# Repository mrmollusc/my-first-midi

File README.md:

# my-first-midi
mmm midi keypad

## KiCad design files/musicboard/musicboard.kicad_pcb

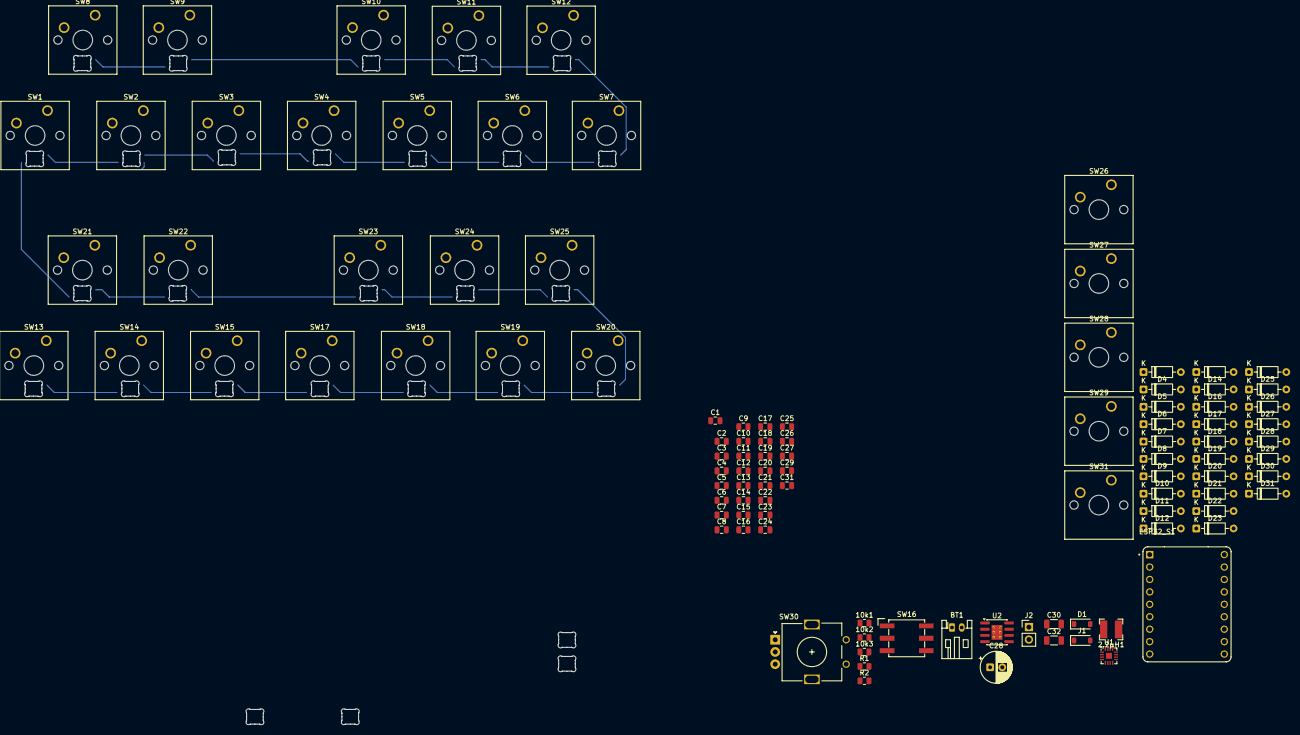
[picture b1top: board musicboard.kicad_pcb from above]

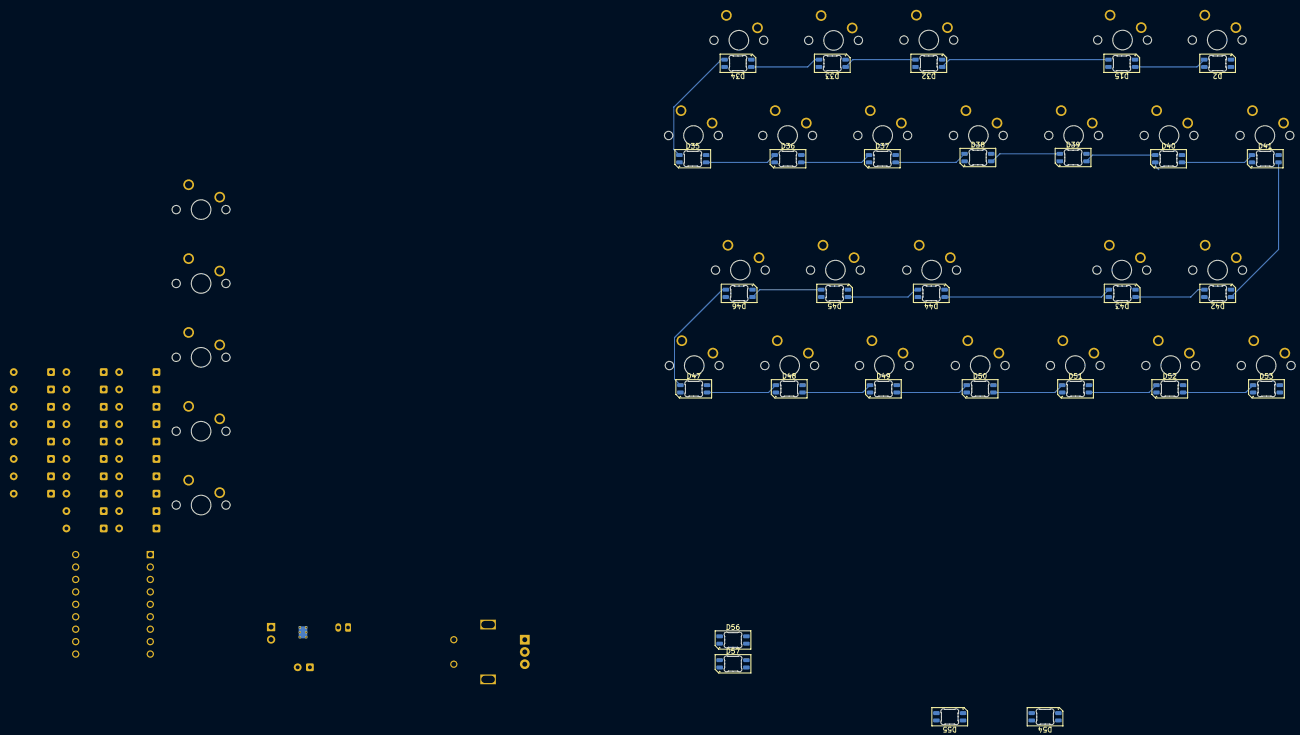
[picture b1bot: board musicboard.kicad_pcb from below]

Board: 2 copper layers, 132 parts (28 on the bottom side), 78 nets.

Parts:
2.2µH1: L_Small; L_Bourns-SRN4018
10k1, 10k2, 10k3: R_Small; R_0805_2012Metric
BT1: Battery_Cell; JST_PH_S2B-PH-K_1x02_P2.00mm_Horizontal
C1, C2, C3, C4, C5, C6, C7, C8, C9, C10, C11, C12, C13, C14, C15, C16, C17, C18, C19, C20, C21, C22, C23, C24, C25, C26, C27, C29, C31: 0.1 µF; C_0805_2012Metric
C28: 470uF; CP_Radial_D6.3mm_P2.50mm
C30: 22 µF; C_1206_3216Metric
C32: 10 µF; C_1206_3216Metric
D1: D_Schottky; D_SOD-123
D2, D15, D32, D33, D34, D35, D36, D37, D38, D39, D40, D41, D42, D43, D44, D45, D46, D47, D48, D49, D50, D51, D52, D53, D54, D55, D56, D57: SK6812MINI-E; LED_SK6812MINI-E_3.2x2.8mm_P1.5mm_ReverseMount
D3, D4, D5, D6, D7, D8, D9, D10, D11, D12, D13, D14, D16, D17, D18, D19, D20, D21, D22, D23, D24, D25, D26, D27, D28, D29, D30, D31: 1N4148; D_DO-35_SOD27_P7.62mm_Horizontal
ESP32_S1: Waveshare ESP32-S3-Zero
J1: Micro_SD_Card; D_SOD-123
J2: Speaker; PinHeader_1x02_P2.54mm_Vertical
R1: 330Ω; R_0805_2012Metric
R2: 1 MΩ; R_0805_2012Metric
SW1, SW2, SW3, SW4, SW5, SW6, SW7, SW8, SW9, SW10, SW11, SW12, SW13, SW14, SW15, SW17, SW18, SW19, SW20, SW21, SW22, SW23, SW24, SW25, SW26, SW27, SW28, SW29, SW31: SW_Push; SW_Cherry_MX_1.00u_PCB
SW16: RotaryEncoder; Nidec_Copal_SH-7010B
SW30: RotaryEncoder; RotaryEncoder_Alps_EC11E_Vertical_H20mm
U1: MAX98357A; TQFN-16-1EP_3x3mm_P0.5mm_EP1.23x1.23mm
U2: IP5306-LC; SOIC-8-1EP_3.9x4.9mm_P1.27mm_EP2.29x3mm_ThermalVias

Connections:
+3.3V: 10k1.2, 10k2.1, 10k3.2
+5V: 2.2µH1.2, C1.1, C2.1, C3.1, C4.1, C5.1, C6.1, C7.1, C8.1, C9.1, C10.1, C11.1, C12.1, C13.1, C14.1, C15.1, C16.1, C17.1, C18.1, C19.1, C20.1, C21.1, C22.1, C23.1, C24.1, C25.1, C26.1, C27.1, C28.1, C29.1, C31.2, C32.2, D1.2 (A), D2.3 (VDD), D15.3 (VDD), D32.3 (VDD), D33.3 (VDD), D34.3 (VDD), D35.3 (VDD), D36.3 (VDD), D37.3 (VDD), D38.3 (VDD), D39.3 (VDD), D40.3 (VDD), D41.3 (VDD), D42.3 (VDD), D43.3 (VDD), D44.3 (VDD), D45.3 (VDD), D46.3 (VDD), D47.3 (VDD), D48.3 (VDD), D49.3 (VDD), D50.3 (VDD), D51.3 (VDD), D52.3 (VDD), D53.3 (VDD), D54.3 (VDD), D55.3 (VDD), D56.3 (VDD), D57.3 (VDD), R2.1, U1.7 (VDD), U1.8 (VDD), U2.8 (VOUT)
/BAT: BT1.1 (+), C30.1, U2.6 (BAT)
/CD: 10k2.2, J1.2 (DAT3/CD_2)
/COL1: SW1.1, SW5.1, SW9.1, SW13.1, SW18.1, SW22.1, SW26.1
/COL2: SW2.1, SW6.1, SW10.1, SW14.1, SW19.1, SW23.1, SW27.1
/COL3: SW3.1, SW7.1, SW11.1, SW15.1, SW20.1, SW24.1, SW28.1
/COL4: SW4.1, SW8.1, SW12.1, SW17.1, SW21.1, SW25.1, SW29.1
/ROW1: D3.1 (K), D4.1 (K), D5.1 (K), D7.1 (K)
/ROW2: D6.1 (K), D8.1 (K), D9.1 (K), D10.1 (K)
/ROW3: D11.1 (K), D12.1 (K), D13.1 (K), D14.1 (K)
/ROW4: D16.1 (K), D17.1 (K), D18.1 (K), D19.1 (K)
/ROW5: D20.1 (K), D21.1 (K), D22.1 (K), D23.1 (K)
/ROW6: D24.1 (K), D25.1 (K), D26.1 (K), D27.1 (K)
/ROW7: D28.1 (K), D29.1 (K), D30.1 (K), D31.1 (K)
/VBUS: D1.1 (K), U2.1 (VIN)
GND: BT1.2 (-), C1.2, C2.2, C3.2, C4.2, C5.2, C6.2, C7.2, C8.2, C9.2, C10.2, C11.2, C12.2, C13.2, C14.2, C15.2, C16.2, C17.2, C18.2, C19.2, C20.2, C21.2, C22.2, C23.2, C24.2, C25.2, C26.2, C27.2, C28.2, C29.2, C30.2, C31.1, C32.1, D2.1 (VSS), D15.1 (VSS), D32.1 (VSS), D33.1 (VSS), D34.1 (VSS), D35.1 (VSS), D36.1 (VSS), D37.1 (VSS), D38.1 (VSS), D39.1 (VSS), D40.1 (VSS), D41.1 (VSS), D42.1 (VSS), D43.1 (VSS), D44.1 (VSS), D45.1 (VSS), D46.1 (VSS), D47.1 (VSS), D48.1 (VSS), D49.1 (VSS), D50.1 (VSS), D51.1 (VSS), D52.1 (VSS), D53.1 (VSS), D54.1 (VSS), D55.1 (VSS), D56.1 (VSS), D57.1 (VSS), SW16.C (C_C), SW30.C, SW31.2, U1.3 (GND), U1.11 (GND), U1.15 (GND), U1.17 (PAD), U2.9 (EP)
unnamed: D2.2 (DIN), R1.2
unnamed: D3.2 (A), SW1.2
unnamed: D4.2 (A), SW2.2
unnamed: D5.2 (A), SW3.2
unnamed: D6.2 (A), SW5.2
unnamed: D7.2 (A), SW4.2
unnamed: D8.2 (A), SW6.2
unnamed: D9.2 (A), SW7.2
unnamed: D10.2 (A), SW8.2
unnamed: D11.2 (A), SW9.2
unnamed: D12.2 (A), SW10.2
unnamed: D13.2 (A), SW11.2
unnamed: D14.2 (A), SW12.2
unnamed: D2.4 (DOUT), D15.2 (DIN)
unnamed: D15.4 (DOUT), D32.2 (DIN)
unnamed: D16.2 (A), SW13.2
unnamed: D17.2 (A), SW14.2
unnamed: D18.2 (A), SW15.2
unnamed: D19.2 (A), SW17.2
unnamed: D20.2 (A), SW18.2
unnamed: D21.2 (A), SW19.2
unnamed: D22.2 (A), SW20.2
unnamed: D23.2 (A), SW21.2
unnamed: D24.2 (A), SW22.2
unnamed: D25.2 (A), SW23.2
unnamed: D26.2 (A), SW24.2
unnamed: D27.2 (A), SW25.2
unnamed: D28.2 (A), SW26.2
unnamed: D29.2 (A), SW27.2
unnamed: D30.2 (A), SW28.2
unnamed: D31.2 (A), SW29.2
unnamed: D32.4 (DOUT), D33.2 (DIN)
unnamed: D33.4 (DOUT), D34.2 (DIN)
unnamed: D34.4 (DOUT), D35.2 (DIN)
unnamed: D35.4 (DOUT), D36.2 (DIN)
unnamed: D36.4 (DOUT), D37.2 (DIN)
unnamed: D37.4 (DOUT), D38.2 (DIN)
unnamed: D38.4 (DOUT), D39.2 (DIN)
unnamed: D39.4 (DOUT), D40.2 (DIN)
unnamed: D40.4 (DOUT), D41.2 (DIN)
unnamed: D41.4 (DOUT), D42.2 (DIN)
unnamed: D42.4 (DOUT), D43.2 (DIN)
unnamed: D43.4 (DOUT), D44.2 (DIN)
unnamed: D44.4 (DOUT), D45.2 (DIN)
unnamed: D45.4 (DOUT), D46.2 (DIN)
unnamed: D46.4 (DOUT), D47.2 (DIN)
unnamed: D47.4 (DOUT), D48.2 (DIN)
unnamed: D48.4 (DOUT), D49.2 (DIN)
unnamed: D49.4 (DOUT), D50.2 (DIN)
unnamed: D50.4 (DOUT), D51.2 (DIN)
unnamed: D51.4 (DOUT), D52.2 (DIN)
unnamed: D52.4 (DOUT), D53.2 (DIN)
unnamed: D53.4 (DOUT), D54.2 (DIN)
unnamed: D54.4 (DOUT), D55.2 (DIN)
unnamed: D55.4 (DOUT), D56.2 (DIN)
unnamed: D56.4 (DOUT), D57.2 (DIN)
unnamed: J2.1, U1.10 (OUTN)
unnamed: J2.2, U1.9 (OUTP)
unnamed: R2.2, U1.4 (~SD_MODE)
unnamed: SW31.1, U2.5 (KEY)
unnamed: 2.2µH1.1, U2.7 (SW)
